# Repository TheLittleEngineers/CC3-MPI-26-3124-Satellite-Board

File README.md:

# CC3-MPI-26-3124-Satellite-Board
The “CC3-MPI-26-3124-Satellite-Board-CoCo-3-Upgrade-2009-V1RA” is a clone of the “Part # AXX-7119 Satellite Board for 26-3124” Multi-Pak Interface CoCo 3 upgrade with the additional feature of being switchable between CoCo 1,2 or 3 mode.

There is an OSHPark Page Here: https://oshpark.com/shared_projects/nOLH7Sm2

Note: the following installation instructions are provided as information
only, and the installer assumes all responsibility in dealing with this
modification.  If you are not absolutely sure you can do this 
modification, and can fix anything you accidently break, it is HIGHLY
suggested you instead take your Multipak Interface to Radio Shack and let 
them have the modification done by their service technicians.  The cost
should be somewhere around $30.

  1. Remove the MPI case
  2. Remove the three screws holding the logic board to the bottom case, 
  leaving the transformer connected.  Remove all the metal clips holding 
  the shield to the bottom of the PCB, noting their positions.  Remove 
  the shield.  This is to avoid melting through the shield insulation 
  while soldering.
  3. Cut the trace coming from pin 52 of IC6 that connects pin 52 of IC6 
  to pin 19 of IC1.
  4. Position the satellite board over IC6, components up, with the 7 
  wires facing towards the card edge.
  5. Connect the 3 yellow wires to IC4 pins 3,9, and 11.  Any order is 
  fine.
  6. Connect the white wire to IC6 pin 52, taking care not to short the 
  leads of IC6.
  7. Connect the blue wire to IC1 pin 19.
  8. Connect the black wire to IC5 pin 8.
  9. Connect the red wire to IC5 pin 16.
  10. Replace the shield and two of the logic board screws.. the one 
  nearest the power switch, and the one near the selector switch.
  11. Place the plastic spacer over the hole for the third screw. 
  Position the hole in the satellite board over the spacer with the 
  components up.  Insert the screw into the board and tighten.  The board 
  must be positioned parallel to the edge card connector so that it fits 
  into the channel between the cabinet top and the cartridge frame.  
  Replace the cabinent top.
  12. Test the unit by connecting it to a CoCo, installing a cartridge in 
  each slot, and checking to see that each slot is selectable and 
  accessable.

Please note: This is derived from an original design by "Little" John Eric and/or his father "Big" John Robert (J.R.) by "Uncle" Robert Allen. It should be thoroughly scrutinized and verified prior to actual use of any kind. DISCLAIMER: The following article is provided for informational purposes only. Any attempt to modify your computer without the proper skills to do so may void your computer. Any attempt to modify your computer without unplugging it first may void you. This Information is provided "as-is" with no guarantee of fitness for any purpose, either explicit or implied. We disclaim any and all responsibility for losses incurred through the use of this information. By using this information, you are deemed to have accepted these conditions of use, and you agree NOT to sue us. CLARIFICATION: The above disclaimer states as plainly as possible that if you decide to make use of any of the information contained within this document that you do so at your own risk. Designing hardware for the CoCo (ColorComputer) and other vintage hardware is a hobby of ours and is not motivated by any desire of profits. As this is a not for profit venture, obviously we can't afford not to disclaim the use of this information.

 PLEASE NOTE: THIS VERSION HAS NOT YET BEEN TESTED.

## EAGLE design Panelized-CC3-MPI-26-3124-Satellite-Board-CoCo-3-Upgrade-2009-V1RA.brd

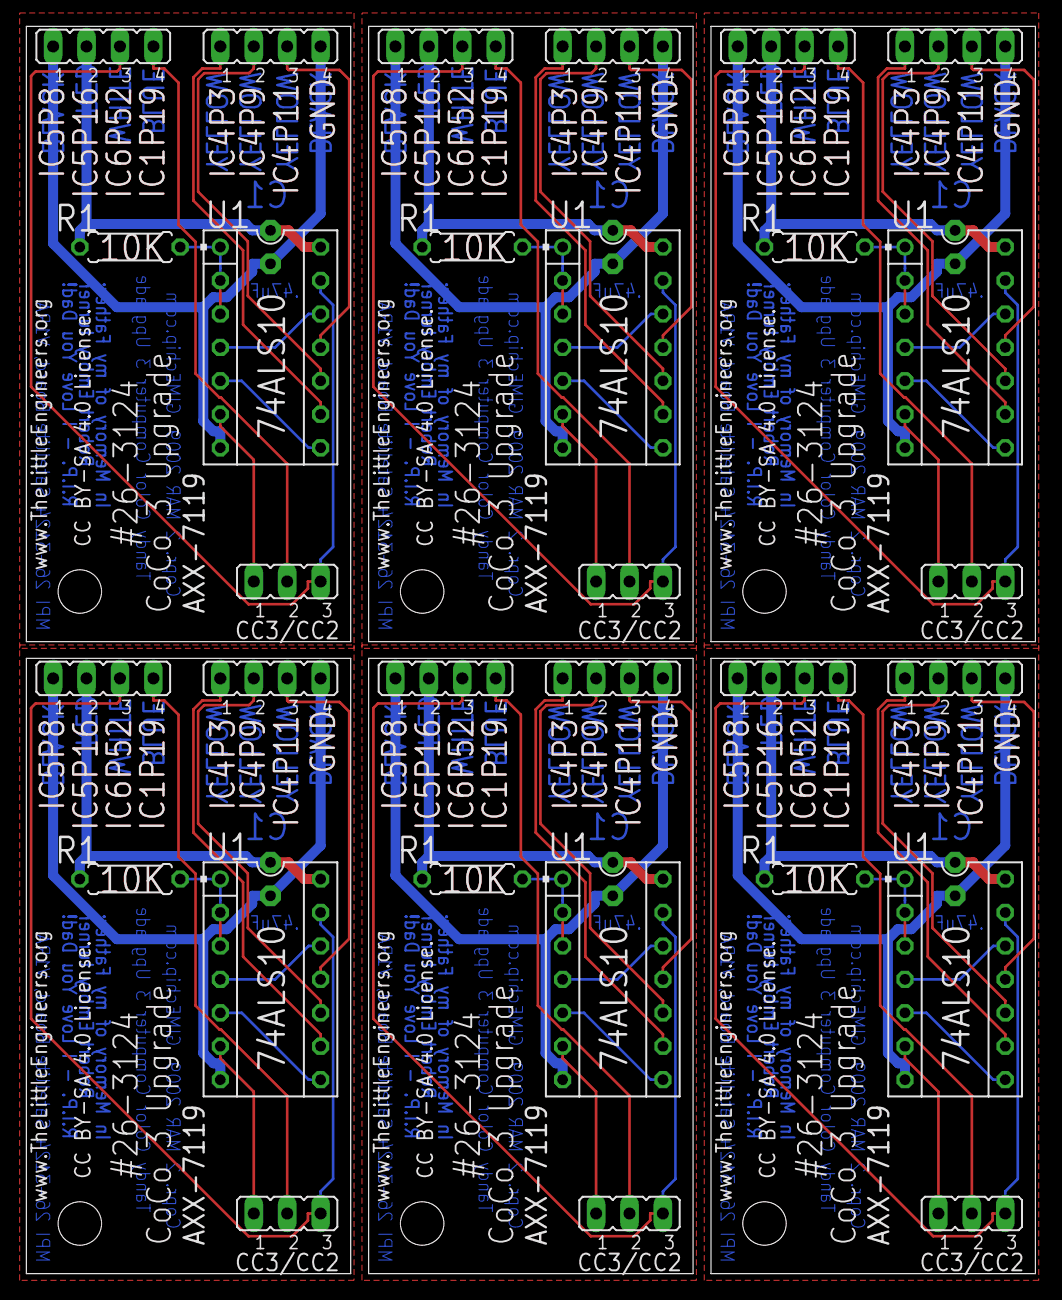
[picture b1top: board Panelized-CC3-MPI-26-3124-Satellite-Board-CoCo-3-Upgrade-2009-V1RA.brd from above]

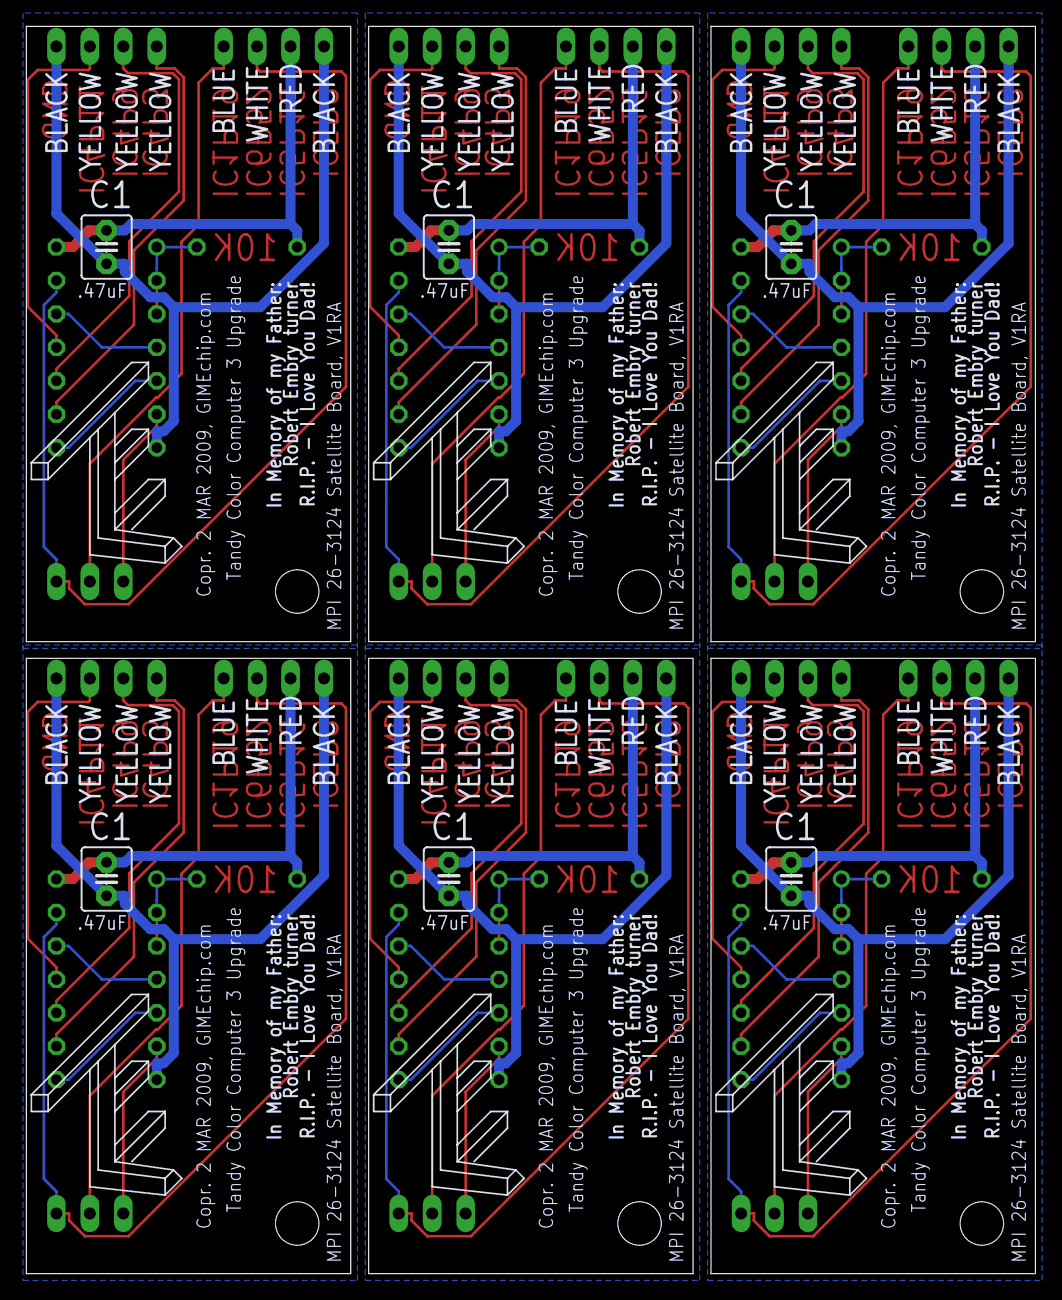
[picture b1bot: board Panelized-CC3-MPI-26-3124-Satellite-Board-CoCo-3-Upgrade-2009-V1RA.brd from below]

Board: 2 copper layers, 76.6 x 94.7 mm, 48 parts (12 on the bottom side), 66 nets.

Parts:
C1, C2, C3, C4, C5, C6: .47uF; C2.5-4
IC1, IC2, IC3, IC4, IC5, IC6: 74ALS10N; DIL14-3
JP1, JP3, JP5, JP6, JP8, JP9, JP11, JP12, JP14, JP15, JP17, JP18: JP4
JP2, JP4, JP7, JP10, JP13, JP16: CC3/CC2; JP2
R1, R2, R3, R4, R5, R6: 10K; 0207/7
U$1, U$3, U$5, U$7, U$9, U$11: SPARKFUN_STAND-OFF
U$2, U$4, U$6, U$8, U$10, U$12: TLE-LOGO-13

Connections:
CC1: IC2.6, JP4.1
CC2: IC3.6, JP7.1
CC3: IC1.6, JP2.1
CC4: IC4.6, JP10.1
CC5: IC5.6, JP13.1
CC6: IC6.6, JP16.1
GND: C1.2, IC1.7, JP1.1, JP3.4
GND1: C2.2, IC2.7, JP5.1, JP6.4
GND2: C3.2, IC3.7, JP8.1, JP9.4
GND3: C4.2, IC4.7, JP11.1, JP12.4
GND4: C5.2, IC5.7, JP14.1, JP15.4
GND5: C6.2, IC6.7, JP17.1, JP18.4
IC1P1: JP4.2, JP5.4
IC1P2: JP7.2, JP8.4
IC1P3: JP10.2, JP11.4
IC1P4: JP13.2, JP14.4
IC1P5: JP16.2, JP17.4
IC1P19: JP1.4, JP2.2
IC4P1: IC2.9, JP6.1
IC4P2: IC2.10, JP6.2
IC4P3: IC1.9, JP3.1
IC4P4: IC2.11, JP6.3
IC4P5: IC3.9, JP9.1
IC4P6: IC3.10, JP9.2
IC4P7: IC3.11, JP9.3
IC4P8: IC4.9, JP12.1
IC4P9: IC1.10, JP3.2
IC4P10: IC4.10, JP12.2
IC4P11: IC1.11, JP3.3
IC4P12: IC4.11, JP12.3
IC4P13: IC5.9, JP15.1
IC4P14: IC5.10, JP15.2
IC4P15: IC5.11, JP15.3
IC4P16: IC6.9, JP18.1
IC4P17: IC6.10, JP18.2
IC4P18: IC6.11, JP18.3
IC6P1: IC2.13, JP4.3, JP5.3
IC6P2: IC3.13, JP7.3, JP8.3
IC6P3: IC4.13, JP10.3, JP11.3
IC6P4: IC5.13, JP13.3, JP14.3
IC6P5: IC6.13, JP16.3, JP17.3
IC6P52: IC1.13, JP1.3, JP2.3
unnamed: IC2.1, IC2.2, IC2.3, R2.1
unnamed: IC2.4, IC2.12
unnamed: IC2.5, IC2.8
unnamed: IC3.1, IC3.2, IC3.3, R3.1
unnamed: IC3.4, IC3.12
unnamed: IC1.1, IC1.2, IC1.3, R1.1
unnamed: IC3.5, IC3.8
unnamed: IC1.4, IC1.12
unnamed: IC1.5, IC1.8
unnamed: IC4.1, IC4.2, IC4.3, R4.1
unnamed: IC4.4, IC4.12
unnamed: IC4.5, IC4.8
unnamed: IC5.1, IC5.2, IC5.3, R5.1
unnamed: IC5.4, IC5.12
unnamed: IC5.5, IC5.8
unnamed: IC6.1, IC6.2, IC6.3, R6.1
unnamed: IC6.4, IC6.12
unnamed: IC6.5, IC6.8
VCC: C1.1, IC1.14, JP1.2, R1.2
VCC1: C2.1, IC2.14, JP5.2, R2.2
VCC2: C3.1, IC3.14, JP8.2, R3.2
VCC3: C4.1, IC4.14, JP11.2, R4.2
VCC4: C5.1, IC5.14, JP14.2, R5.2
VCC5: C6.1, IC6.14, JP17.2, R6.2

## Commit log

2019-08-01 Maintenance

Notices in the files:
Panelized-CC3-MPI-26-3124-Satellite-Board-CoCo-3-Upgrade-2009-V1RA.brd:
CC BY-SA 4.0 License.
parts and their libraries:
RetroZilla.org-74xx-us: Copyright ©07 Jan 2013, by:
John Eric Turner and his Father.
sales@GIMEchip.comLicensed to:
http://www.RetroZilla.org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
